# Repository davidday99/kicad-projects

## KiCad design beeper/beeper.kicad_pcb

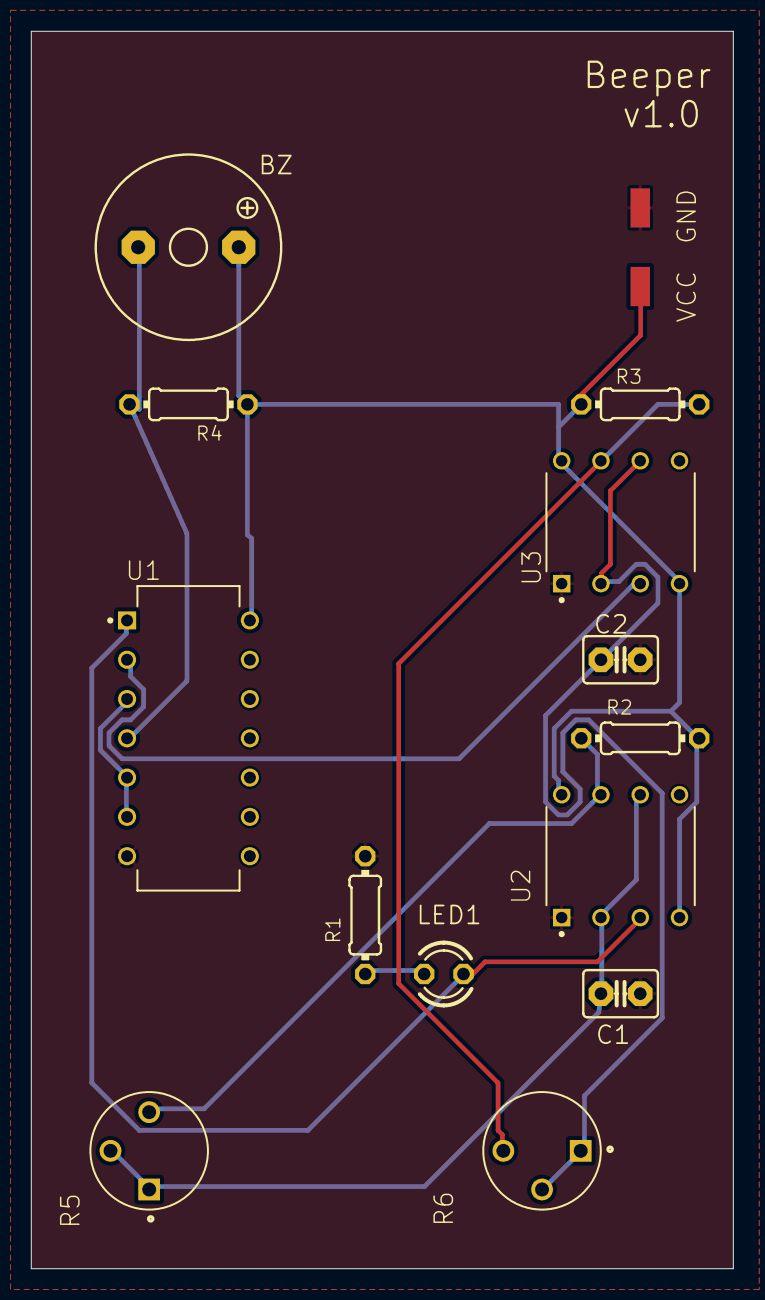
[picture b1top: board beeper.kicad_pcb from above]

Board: 2 copper layers, 45.4 x 80.0 mm, 15 parts (0 on the bottom side), 11 nets.

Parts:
BZ: F/QMBIII; F_QMBIII
C1: 1.44uF; C2.5-3
C2: 1.82nF; C2.5-3
GND: SMD1,27-2,54
LED1: RED; LED3MM
R1: 220; 0204_7
R2, R3, R4: 1K; 0204_7
R5: SPEED; TO250P760H635-3_PV12P105A01B00
R6: TONE; TO250P760H635-3_PV12P105A01B00
U1: CD4011BE; DIP794W45P254L1969H508Q14
U2, U3: LMC555CN; DIP794W45P254L959H508Q8
VCC: SMD1,27-2,54

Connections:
GND: C1.2, C2.2, GND.1, R1.2, U1.7, U2.1, U3.1
unnamed: R2.1, R5.3, U2.7
unnamed: C1.1, R5.1, R5.2, U2.2, U2.6
unnamed: LED1.A, U1.1, U2.3
unnamed: LED1.K, R1.1
unnamed: R3.1, R6.3, U3.7
unnamed: C2.1, R6.1, R6.2, U3.2, U3.6
unnamed: U1.2, U3.3
unnamed: U1.3, U1.5, U1.6
unnamed: BZ.-, R4.2, U1.4
VCC: BZ.+, R2.2, R3.2, R4.1, U1.14, U2.4, U2.8, U3.4, U3.8, VCC.1

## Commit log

2023-03-28 add beeper_smt project
